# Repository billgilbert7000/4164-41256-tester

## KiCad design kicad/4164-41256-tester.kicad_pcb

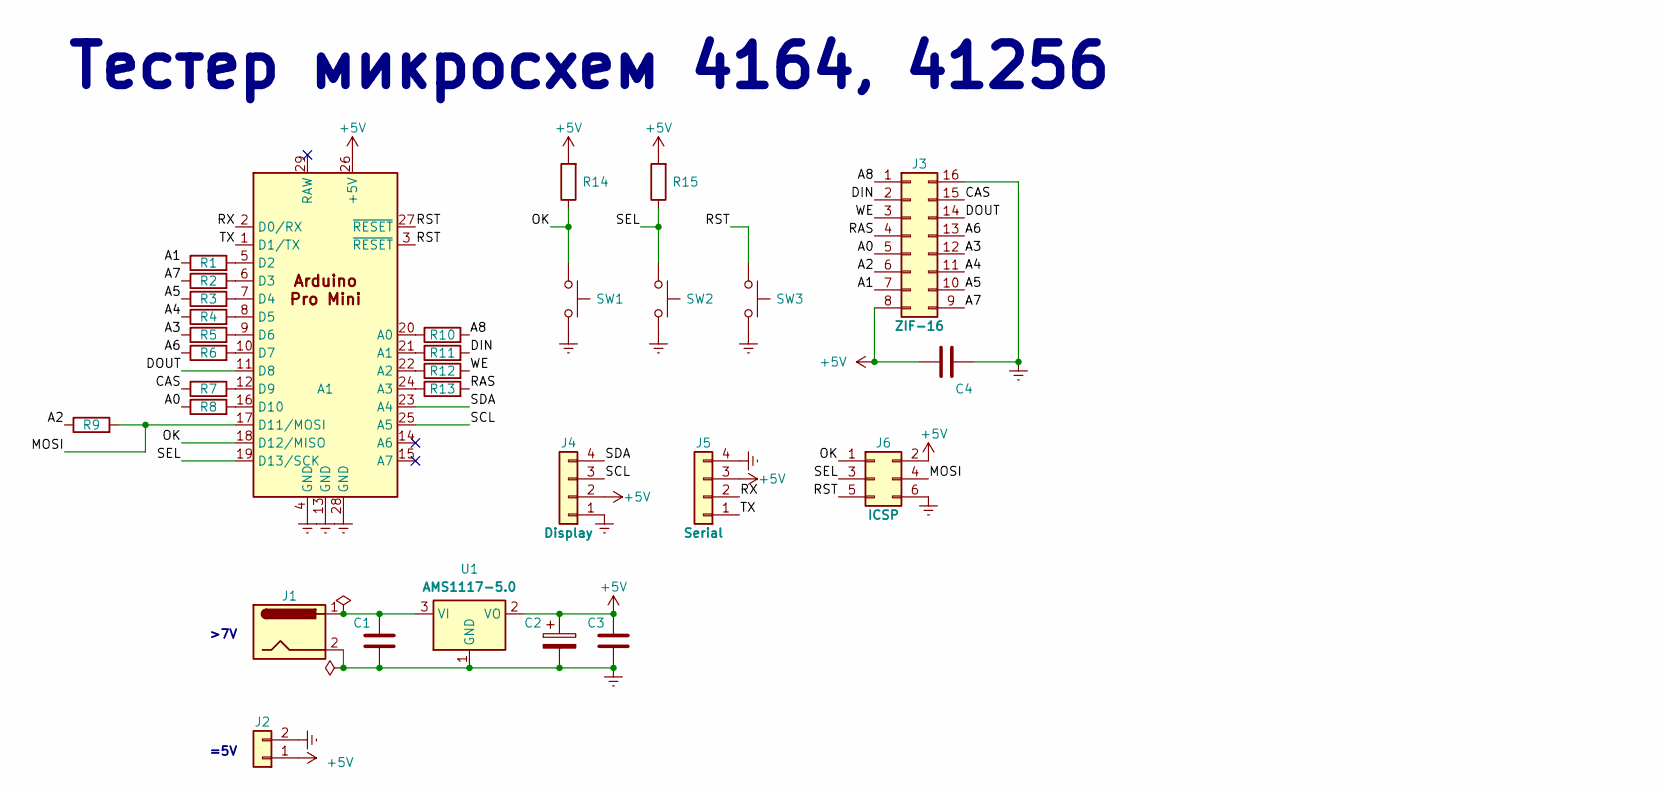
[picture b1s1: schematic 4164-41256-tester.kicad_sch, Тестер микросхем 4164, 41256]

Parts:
A1: Arduino Pro Mini; arduino_pro_mini
C1, C3, C4: 100 nF; C_0805_2012Metric_Pad1.18x1.45mm_HandSolder
C2: 1000 uF; CP_Radial_D8.0mm_P3.50mm
J1: Jack DC; BarrelJack_Horizontal
J2: PCB Terminal Block; DG301-5.0-2P-1X
J3: ZIF-16; DIP_Socket-16_W4.3_W5.08_W7.62_W10.16_W10.9_3M_216-3340-00-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
J4: Display; SSD1306-0.91-OLED-4pin-128x32
J5: Serial; PinHeader_1x04_P2.54mm_Vertical
J6: ICSP; PinHeader_2x03_P2.54mm_Vertical
R1, R2, R3, R4, R5, R6, R7, R8, R9, R10, R11, R12, R13: 47; R_0805_2012Metric_Pad1.20x1.40mm_HandSolder
R14, R15: 10K; R_0805_2012Metric_Pad1.20x1.40mm_HandSolder
SW1, SW2, SW3: SW Push; SW_PUSH_6mm
U1: AMS1117-5.0; SOT-223-3_TabPin2

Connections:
+5V: A1.26 (+5V), C2.1, C3.1, C4.1, J2.1, J3.8, J4.2, J5.3, J6.2, R14.2, R15.2, U1.2 (VO)
/A0: J3.5, R8.1
/A1: J3.7, R1.1
/A2: J3.6, R9.1
/A3: J3.12, R5.1
/A4: J3.11, R4.1
/A5: J3.10, R3.1
/A6: J3.13, R6.1
/A7: J3.9, R2.1
/A8: J3.1, R10.2
/CAS: J3.15, R7.1
/DIN: J3.2, R11.2
/DOUT: A1.11 (D8), J3.14
/MOSI: A1.17 (D11/MOSI), J6.4, R9.2
/OK: A1.18 (D12/MISO), J6.1, R14.1, SW1.1
/RAS: J3.4, R13.2
/RST: A1.3 (~RESET), A1.27 (~RESET), J6.5, SW3.1
/RX: A1.2 (D0/RX), J5.2
/SCL: A1.25 (A5), J4.3
/SDA: A1.23 (A4), J4.4
/SEL: A1.19 (D13/SCK), J6.3, R15.1, SW2.1
/TX: A1.1 (D1/TX), J5.1
/WE: J3.3, R12.2
Earth: A1.4 (GND), A1.13 (GND), A1.28 (GND), C1.2, C2.2, C3.2, C4.2, J1.2, J2.2, J3.16, J4.1, J5.4, J6.6, SW1.2, SW2.2, SW3.2, U1.1 (GND)
unnamed: A1.20 (A0), R10.1
unnamed: A1.21 (A1), R11.1
unnamed: A1.22 (A2), R12.1
unnamed: A1.24 (A3), R13.1
unnamed: A1.5 (D2), R1.2
unnamed: A1.6 (D3), R2.2
unnamed: A1.7 (D4), R3.2
unnamed: A1.8 (D5), R4.2
unnamed: A1.9 (D6), R5.2
unnamed: A1.10 (D7), R6.2
unnamed: A1.12 (D9), R7.2
unnamed: A1.16 (D10), R8.2
unnamed: C1.1, J1.1, U1.3 (VI)

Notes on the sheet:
=5V
Тестер микросхем 4164, 41256
>7V

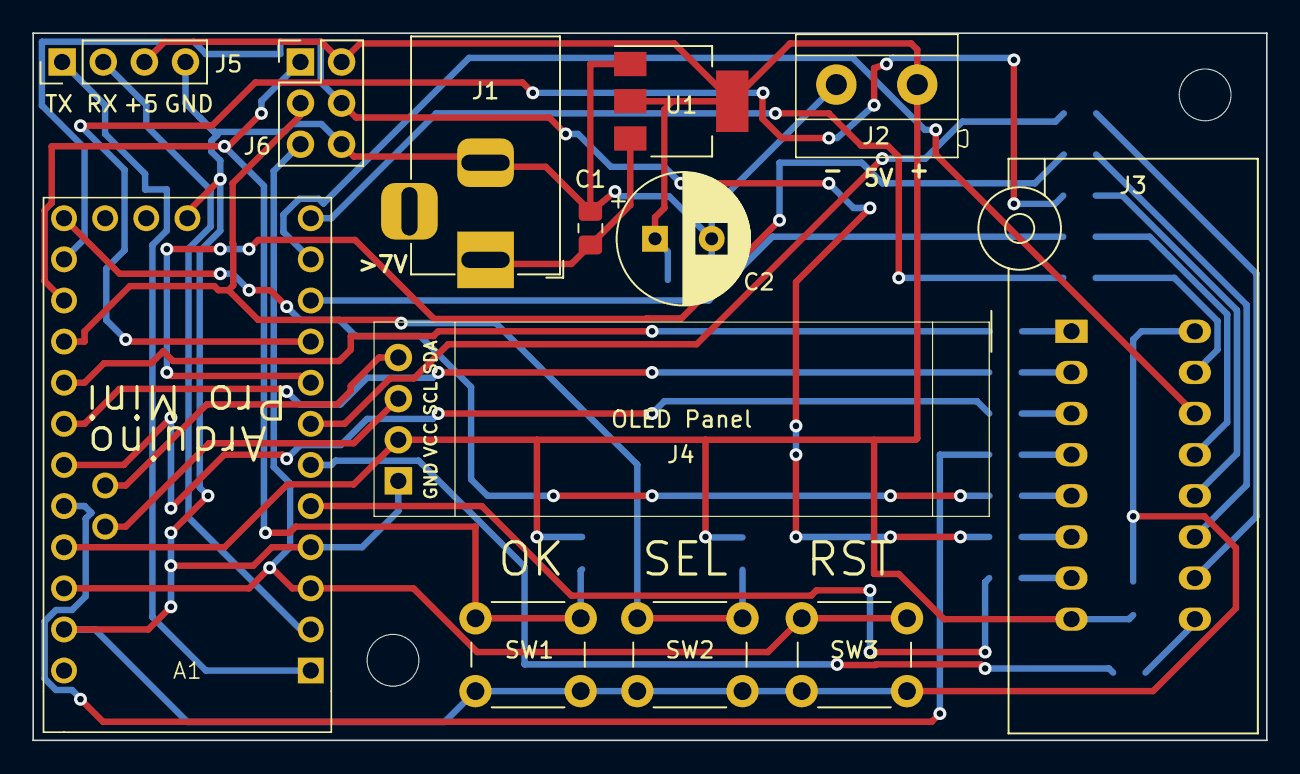
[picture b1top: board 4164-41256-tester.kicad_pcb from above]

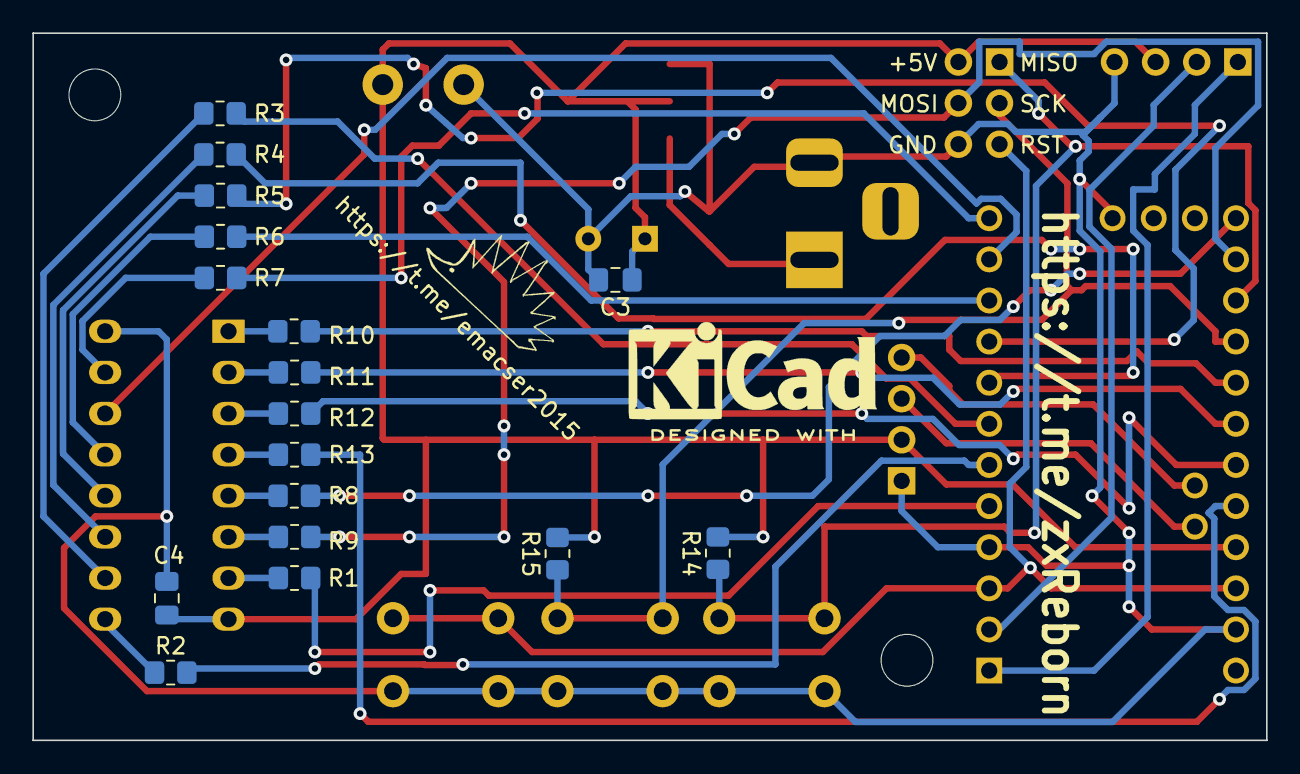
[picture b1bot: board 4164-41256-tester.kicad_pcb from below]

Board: 2 copper layers, 76.2 x 43.7 mm, 30 parts (17 on the bottom side), 37 nets.

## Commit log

2023-09-03 init commit
2023-09-10 add ibom
2023-09-16 add scheme in pdf
2023-09-16 moving ibom
2023-09-16 fix .gitignore
2023-09-16 add gerbers
2023-09-24 start code from old
2023-09-24 remove EPROM operation
2023-09-24 add .gitignore
2023-09-24 add config file
2023-09-24 remove serial
2023-09-24 remove animation
2023-09-24 first test for 4164
2023-10-01 add images
2023-10-15 remove char.ino
2023-10-15 remove unused code
2023-10-15 fix style
2023-10-21 new main loop
2023-10-21 add impl for ctor for Executor
2023-10-21 add Executor::init
2023-10-21 add dumbs for Executor::go, about
2023-10-21 add impl for Buttons::wait_ok
2023-10-21 fix Executor::about
2023-10-21 add Executor::init_dram
2023-10-21 add impl for Executor::fillx
2023-10-21 add impl for Executor::error
2023-10-21 add impl for Executor::read_address
2023-10-21 add impl for Executor::write_address
2023-10-21 add impl for Executor::set_bus
2023-10-21 add impl for Executor::set_mode
2023-10-21 fix Executor::test
2023-10-21 add impl for Executor::readonly
2023-10-21 fix messages
2023-10-21 enable greeting
2023-10-29 fix for 2.1.0
2023-10-29 add new pics
2023-10-29 add pic
